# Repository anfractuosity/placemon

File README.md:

# placemon

The idea is to use the data collected from a number of sensors along with machine learning techniques to recognise different events occurring in your home.  For example processing audio data, to see if you have left a tap running.

One of the key inspirations is the paper - "Synthetic Sensors: Towards General-Purpose Sensing", I noticed some of the sensors used alone on their board such as the GridEye thermal sensor appear to be pretty expensive.  I've tried to select a smaller set of sensors that will hopefully allow us to achieve a similar level of accuracy at detecting different events.

# Sensors

* LSM303AGR - accelerometer and compass
* SHT30-DIS - temperature and humidity sensor
* GMA4030H11-F26 - PDM microphone
* VL6180V1NR - Laser ToF sensor

# To Do

* Ooops - 2.54mm pin header is in slightly wrong location, so mounting holes won't be usable currently

# Testing

Install:

```
sudo apt install python3-pip
```

Libraries for microphone:
```
sudo apt install libasound2-dev libportaudio2 libsndfile1
pip3 install sounddevice soundfile
```

Libraries for temperature and accelerometer:
```
pip3 install adafruit-circuitpython-sht31d
pip3 install adafruit-circuitpython-lsm303-accel adafruit-circuitpython-lis2mdl
```

Run:
```
import board
import busio
import adafruit_sht31d
import adafruit_lsm303_accel
import adafruit_lis2mdl

i2c = board.I2C()
accel = adafruit_lsm303_accel.LSM303_Accel(i2c)
mag = adafruit_lis2mdl.LIS2MDL(i2c)
sensor = adafruit_sht31d.SHT31D(i2c)

print("Acceleration (m/s^2): X=%0.3f Y=%0.3f Z=%0.3f"%accel.acceleration)
print("Magnetometer (micro-Teslas)): X=%0.3f Y=%0.3f Z=%0.3f"%mag.magnetic)
print('Humidity: {0}%'.format(sensor.relative_humidity))
print('Temperature: {0}C'.format(sensor.temperature))
```

# Audio 

Uses PDM driver from https://github.com/imec-int/Raspberry-Pi-Installer-Scripts

Changed the following lines, to the suggestion:

```
/home/pi/Raspberry-Pi-Installer-Scripts/pdm_mic_module/linux_bcm2835_kernel/bcm2835-i2s.c:792:3: error: ‘struct snd_soc_dai_driver’ has no member named ‘symmetric_rates’; did you mean ‘symmetric_rate’?
/home/pi/Raspberry-Pi-Installer-Scripts/pdm_mic_module/linux_bcm2835_kernel/bcm2835-i2s.c:793:3: error: ‘struct snd_soc_dai_driver’ has no member named ‘symmetric_samplebits’; did you mean ‘symmetric_sample_bits’?
```

```
arecord --device="plughw:0,0" -f S16_LE -r 44100 out.wav
```

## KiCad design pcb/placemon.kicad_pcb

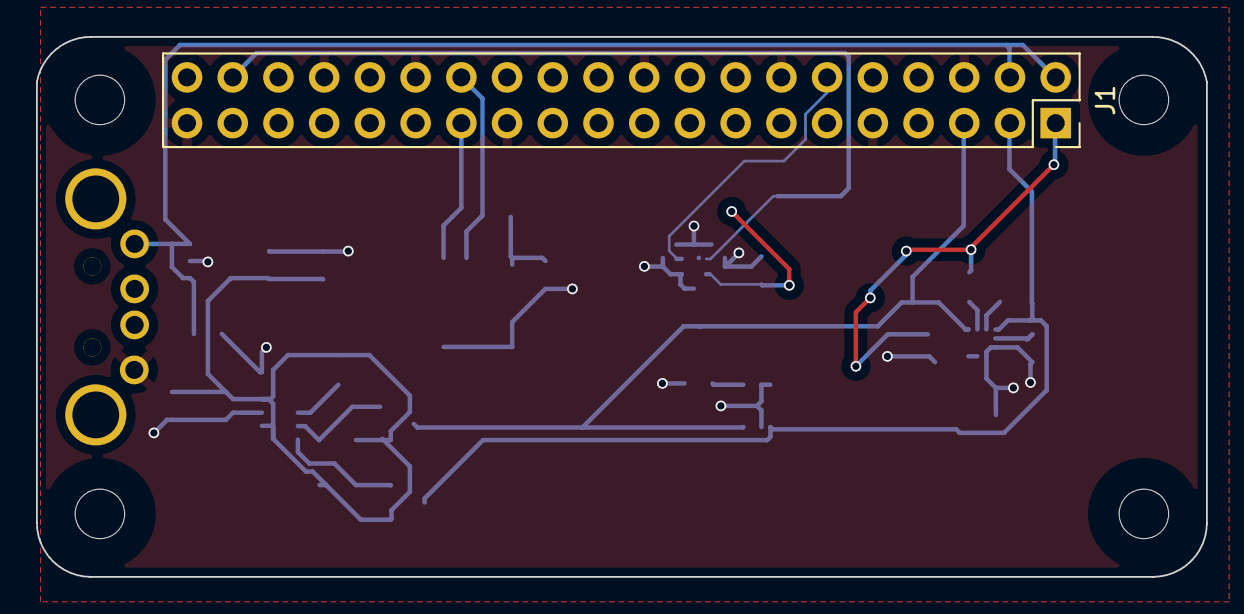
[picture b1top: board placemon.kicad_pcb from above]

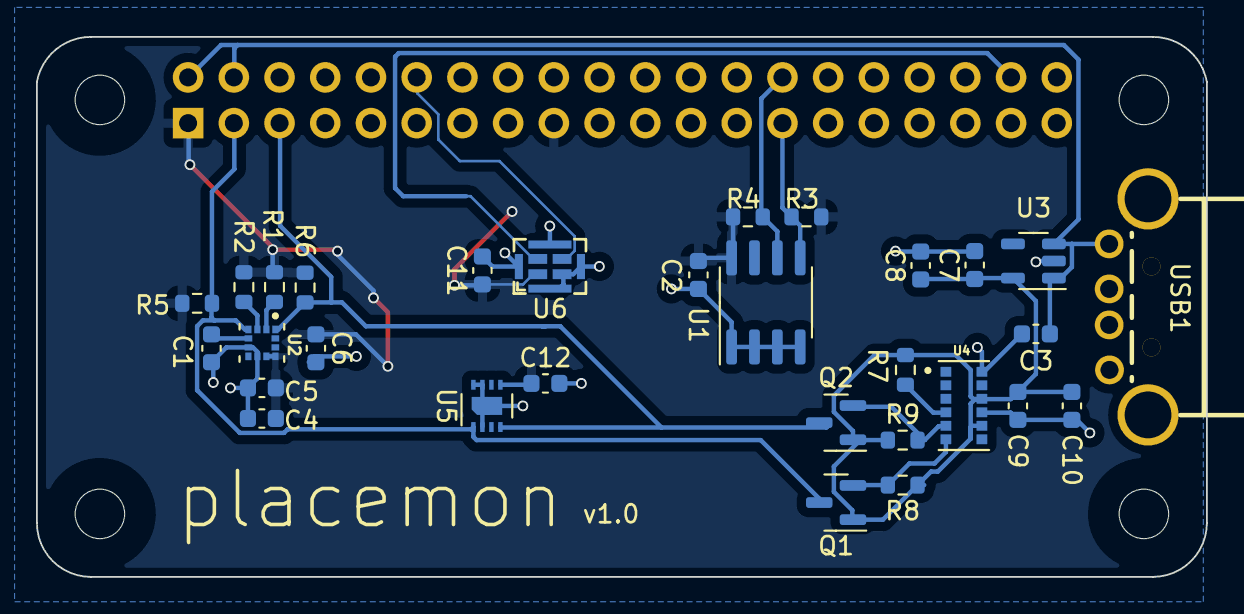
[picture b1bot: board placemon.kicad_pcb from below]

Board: 2 copper layers, 65.0 x 30.0 mm, 31 parts (30 on the bottom side), 16 nets.

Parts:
C1: 220nF; C_0603_1608Metric
C2: 100n; C_0603_1608Metric
C3, C4, C7: 10uF; C_0603_1608Metric
C5, C6, C9: 100nF; C_0603_1608Metric
C8, C11, C12: 0.1uF; C_0603_1608Metric
C10: 4.7uF; C_0603_1608Metric
J1: RPi_GPIO; PinSocket_2x20_P2.54mm_Vertical
Q1, Q2: BSS138; SOT-23
R1, R2: 10K; R_0603_1608Metric
R3, R4, R5, R6, R8, R9: 3.9K; R_0603_1608Metric
R7: 47K; R_0603_1608Metric
U1: CAT24C128; SOIC-8_3.9x4.9mm_P1.27mm
U2: LSM303AGR; PQFN50P200X200X100-12N
U3: LP5907MFX-2.8; SOT-23-5
U4: VL6180V1NR/1; XDCR_VL6180V1NR_1
U5: SHT30-DIS; Sensirion_DFN-8-1EP_2.5x2.5mm_P0.5mm_EP1.1x1.7mm
U6: GMA4030H11-F26
USB1: AM90; USB-AM-TH_AM90

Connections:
+2V8: C7.1, C8.1, C9.1, C10.1, Q1.1 (G), Q2.1 (G), R7.1, R8.1, R9.1, U3.5 (OUT), U4.8 (AVDD_VCSEL), U4.10 (AVDD)
+3V3: C2.1, C4.1, C5.1, C6.1, C11.1, C12.1, J1.1 (3.3V), J1.17 (3.3V), R1.1, R2.1, R3.1, R4.1, R5.1, R6.1, U1.8 (VCC), U2.9 (VDD), U2.10 (VDD_IO), U5.5 (VDD), U6.1 (VDD)
+5V: C3.1, J1.2 (5V), J1.4 (5V), U3.1 (IN), U3.3 (EN), USB1.1 (VCC)
GND: C1.2, C2.2, C3.2, C4.2, C5.2, C6.2, C7.2, C8.2, C9.2, C10.2, C11.2, C12.2, J1.6 (GND), J1.9 (GND), J1.14 (GND), J1.20 (GND), J1.25 (GND), J1.30 (GND), J1.34 (GND), J1.39 (GND), U1.1 (A0), U1.2 (A1), U1.3 (A2), U1.4 (GND), U2.6 (GND), U2.8 (GND), U3.2 (GND), U4.9 (AVSS_VCSEL), U4.12 (GND), U5.2 (ADDR), U5.7 (R), U5.8 (VSS), U5.9 (VSS), U6.2 (SELECT), U6.5 (GND), U6.6 (GND), U6.7 (GND), U6.8 (GND), USB1.4 (GND)
ID_SC: J1.28 (ID_SC), R4.2, U1.6 (SCL)
ID_SD: J1.27 (ID_SD), R3.2, U1.5 (SDA)
unnamed: C1.1, U2.5 (C1)
unnamed: R1.2, U2.2 (CS_XL)
unnamed: R2.2, U2.3 (CS_MAG)
unnamed: R7.2, U4.4 (GPIO0/CE)
SCK: J1.5 (GPIO03_SCL1_I2C), Q2.3 (D), R6.2, U2.1 (SCL/SPC), U5.4 (SCL)
SCK_2V8: Q2.2 (S), R9.2, U4.5 (SCL)
SDA: J1.3 (GPIO02_SDA1_I2C), Q1.3 (D), R5.2, U2.4 (SDA/SDI/SDO), U5.1 (SDA)
SDA_2V8: Q1.2 (S), R8.2, U4.6 (SDA)
clock: J1.12 (GPIO18), U6.3 (CLOCK)
data: J1.38 (GPIO20), U6.4 (DATA)

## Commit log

2022-06-08 Initial
2022-06-08 Image
2022-06-08 Readme
2022-06-08 Intro
2022-06-08 Testing
2022-06-08 Assembled
2022-06-08 Audio
2022-06-08 Try to fix position of pin header
2022-06-08 Fix horizontal position of pin header
2022-06-08 Fix DRC issues
2022-06-11 Grafana and InfluxDB setup with docker
2022-06-11 Dashboard
2022-06-12 Update libraries and dashboard
2022-06-12 Fix README
2022-06-12 Update each query to retun less data
